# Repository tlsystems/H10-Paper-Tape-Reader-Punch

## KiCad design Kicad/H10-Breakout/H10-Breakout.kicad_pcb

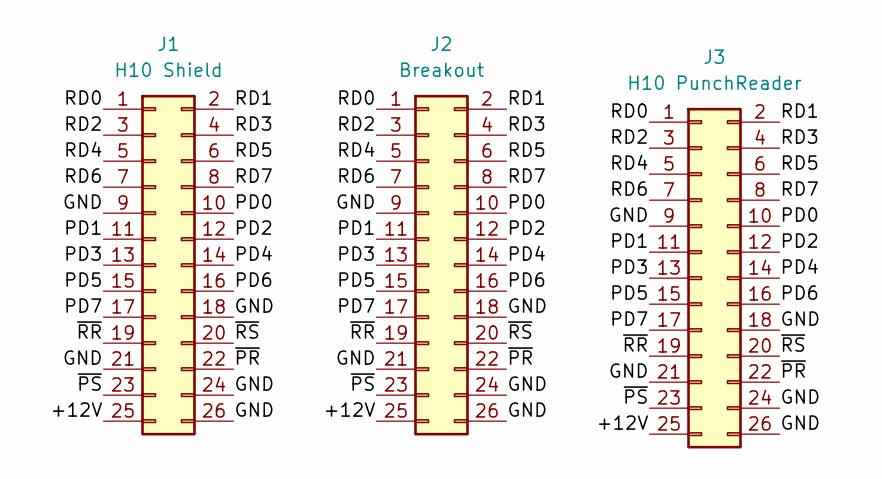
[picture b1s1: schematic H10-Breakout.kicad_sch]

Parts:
J1: H10 Shield; PinSocket_2x13_P2.54mm_Vertical
J2: Breakout; PinHeader_2x13_P2.54mm_Vertical
J3: H10 PunchReader; PinHeader_2x13_P2.54mm_Vertical

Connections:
/+12V: J1.25, J2.25, J3.25
/GND: J1.9, J1.18, J1.21, J1.24, J1.26, J2.9, J2.18, J2.21, J2.24, J2.26, J3.9, J3.18, J3.21, J3.24, J3.26
/PD0: J1.10, J2.10, J3.10
/PD1: J1.11, J2.11, J3.11
/PD2: J1.12, J2.12, J3.12
/PD3: J1.13, J2.13, J3.13
/PD4: J1.14, J2.14, J3.14
/PD5: J1.15, J2.15, J3.15
/PD6: J1.16, J2.16, J3.16
/PD7: J1.17, J2.17, J3.17
/RD0: J1.1, J2.1, J3.1
/RD1: J1.2, J2.2, J3.2
/RD2: J1.3, J2.3, J3.3
/RD3: J1.4, J2.4, J3.4
/RD4: J1.5, J2.5, J3.5
/RD5: J1.6, J2.6, J3.6
/RD6: J1.7, J2.7, J3.7
/RD7: J1.8, J2.8, J3.8
/~PR: J1.22, J2.22, J3.22
/~PS: J1.23, J2.23, J3.23
/~RR: J1.19, J2.19, J3.19
/~RS: J1.20, J2.20, J3.20

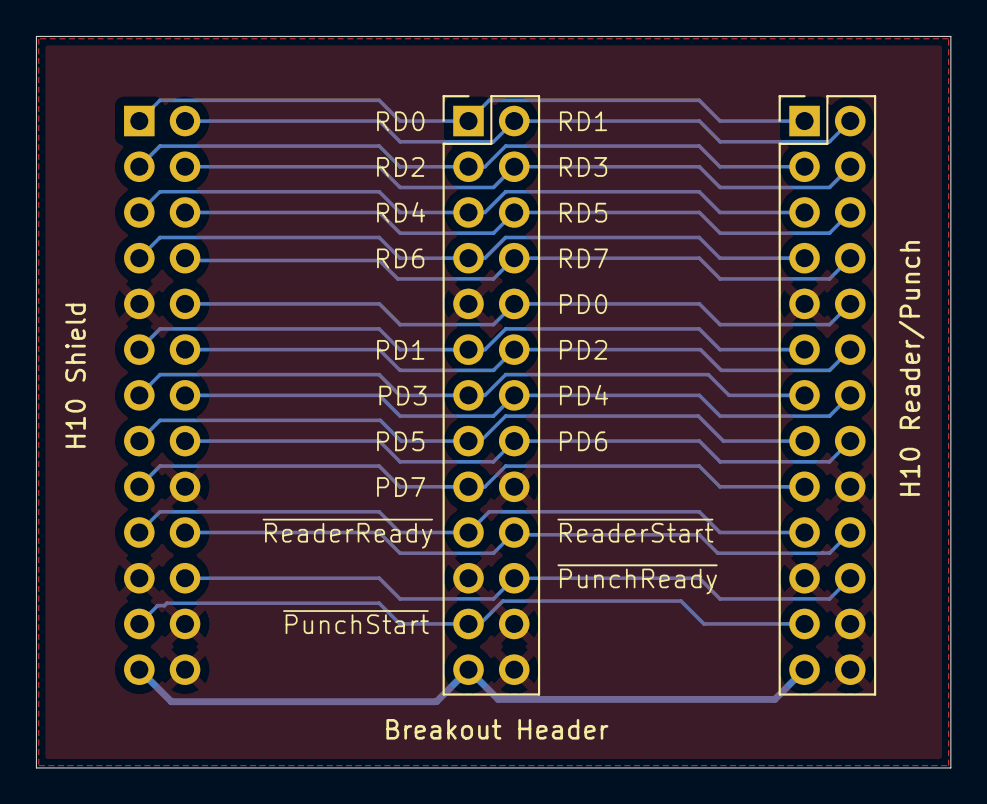
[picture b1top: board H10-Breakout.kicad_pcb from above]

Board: 2 copper layers, 50.8 x 40.6 mm, 3 parts (1 on the bottom side), 22 nets.

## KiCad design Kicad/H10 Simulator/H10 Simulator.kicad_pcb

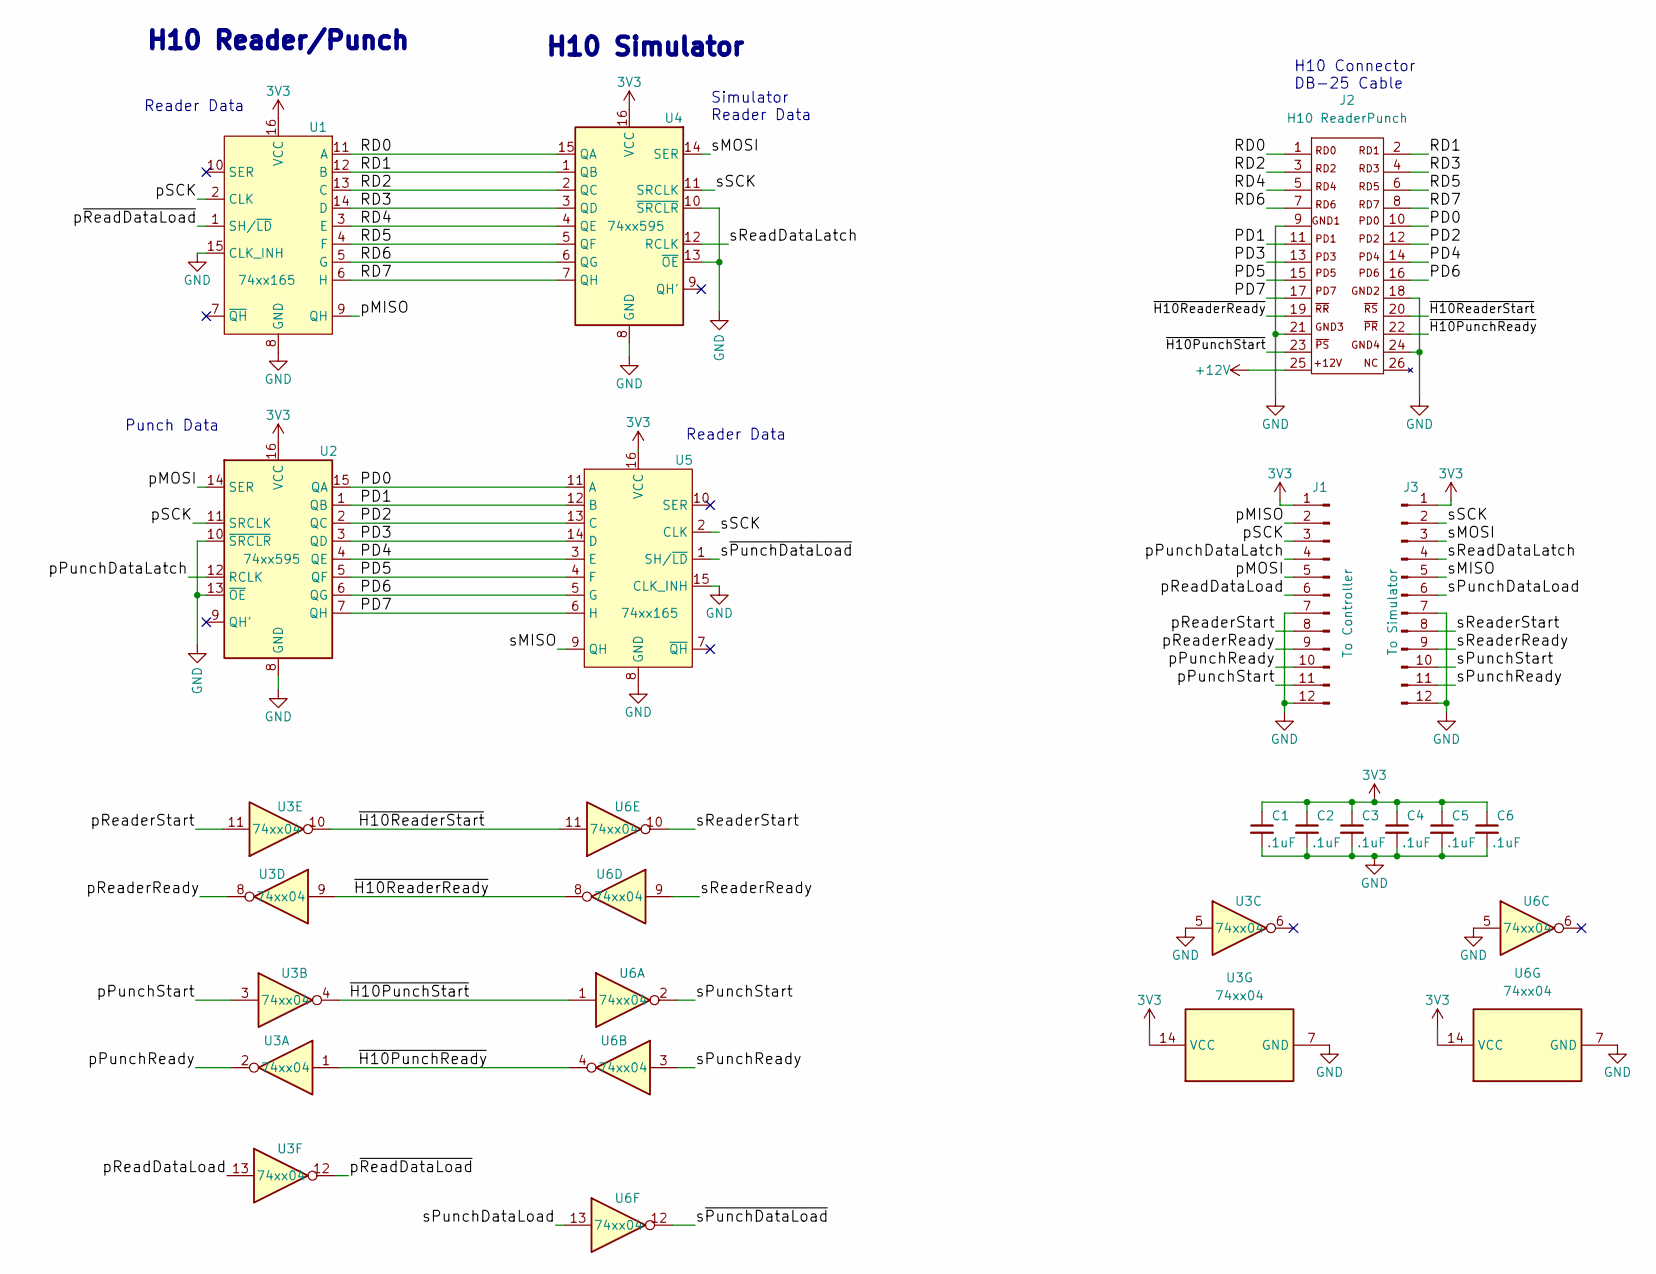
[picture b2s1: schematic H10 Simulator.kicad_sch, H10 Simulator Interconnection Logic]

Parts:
C1, C2, C3, C4, C5, C6: .1uF; C_0603_HandSoldering
J1: To Controller; PinHeader_1x12_P2.54mm_Vertical
J2: H10 ReaderPunch; PinHeader_2x13_P2.54mm_Vertical
J3: To Simulator; PinHeader_1x12_P2.54mm_Vertical
U1, U5: 74xx165; SOIC-16_3.9x9.9mm_P1.27mm
U2, U4: 74xx595; SOIC-16_3.9x9.9mm_P1.27mm
U3, U6: 74xx04; SOIC-14_3.9x8.7mm_P1.27mm

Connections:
3V3: C1.1, C2.1, C3.1, C4.1, C5.1, C6.1, J1.1, J3.1, U1.16 (VCC), U2.16 (VCC), U3.14 (VCC), U4.16 (VCC), U5.16 (VCC), U6.14 (VCC)
+12V: J2.25
/PD0: J2.10, U2.15 (QA), U5.11 (A)
/PD1: J2.11, U2.1 (QB), U5.12 (B)
/PD2: J2.12, U2.2 (QC), U5.13 (C)
/PD3: J2.13, U2.3 (QD), U5.14 (D)
/PD4: J2.14, U2.4 (QE), U5.3 (E)
/PD5: J2.15, U2.5 (QF), U5.4 (F)
/PD6: J2.16, U2.6 (QG), U5.5 (G)
/PD7: J2.17, U2.7 (QH), U5.6 (H)
/RD0: J2.1, U1.11 (A), U4.15 (QA)
/RD1: J2.2 (RD1), U1.12 (B), U4.1 (QB)
/RD2: J2.3, U1.13 (C), U4.2 (QC)
/RD3: J2.4, U1.14 (D), U4.3 (QD)
/RD4: J2.5, U1.3 (E), U4.4 (QE)
/RD5: J2.6, U1.4 (F), U4.5 (QF)
/RD6: J2.7, U1.5 (G), U4.6 (QG)
/RD7: J2.8, U1.6 (H), U4.7 (QH)
/pMISO: J1.2, U1.9 (QH)
/pMOSI: J1.5, U2.14 (SER)
/pPunchDataLatch: J1.4, U2.12 (RCLK)
/pPunchReady: J1.10, U3.2
/pPunchStart: J1.11, U3.3
/pReadDataLoad: J1.6, U3.13
/pReaderReady: J1.9, U3.8
/pReaderStart: J1.8, U3.11
/pSCK: J1.3, U1.2 (CLK), U2.11 (SRCLK)
/p~ReadDataLoad: U1.1 (SH/~LD), U3.12
/sMISO: J3.5, U5.9 (QH)
/sMOSI: J3.3, U4.14 (SER)
/sPunchDataLoad: J3.6, U6.13
/sPunchReady: J3.11, U6.3
/sPunchStart: J3.10, U6.2
/sReadDataLatch: J3.4, U4.12 (RCLK)
/sReaderReady: J3.9, U6.9
/sReaderStart: J3.8, U6.10
/sSCK: J3.2, U4.11 (SRCLK), U5.2 (CLK)
/s~PunchDataLoad: U5.1 (SH/~LD), U6.12
/~H10PunchReady: J2.22, U3.1, U6.4
/~H10PunchStart: J2.23, U3.4, U6.1
/~H10ReaderReady: J2.19, U3.9, U6.8
/~H10ReaderStart: J2.20, U3.10, U6.11
GND: C1.2, C2.2, C3.2, C4.2, C5.2, C6.2, J1.7, J1.12, J2.9, J2.18 (GND2), J2.21, J2.24, J3.7, J3.12, U1.8 (GND), U1.15 (CLK_INH), U2.8 (GND), U2.10 (~SRCLR), U2.13 (~OE), U3.5, U3.7 (GND), U4.8 (GND), U4.10 (~SRCLR), U4.13 (~OE), U5.8 (GND), U5.15 (CLK_INH), U6.5, U6.7 (GND)

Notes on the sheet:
Reader Data
Punch Data
H10 Simulator
Simulator Reader Data
H10 Reader/Punch
H10 Connector DB-25 Cable

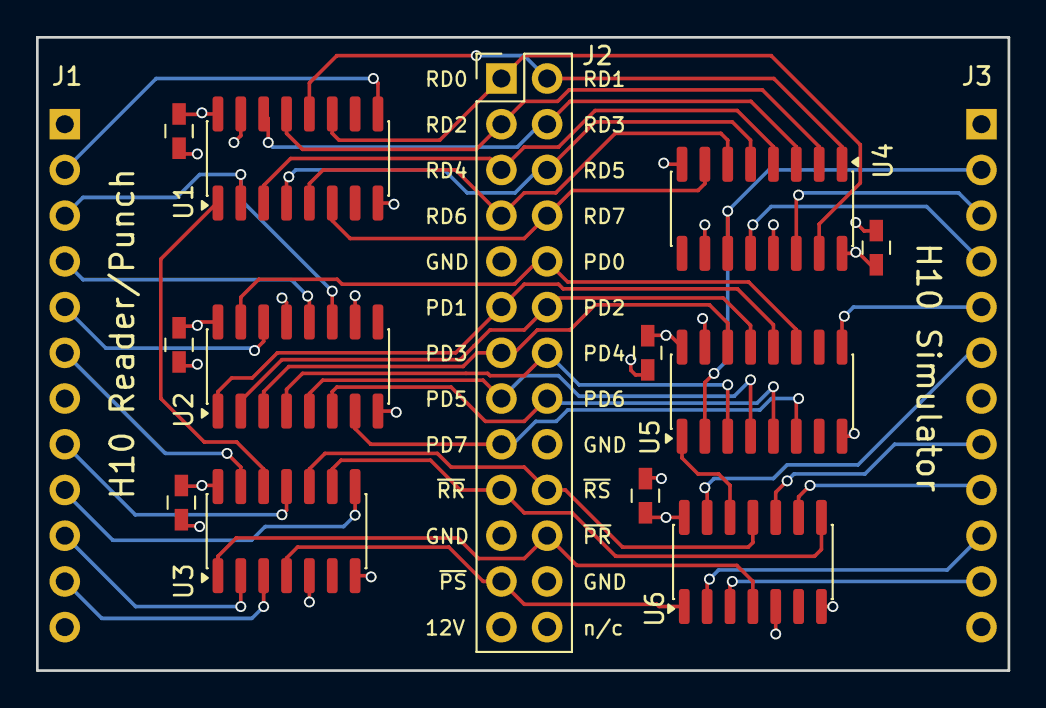
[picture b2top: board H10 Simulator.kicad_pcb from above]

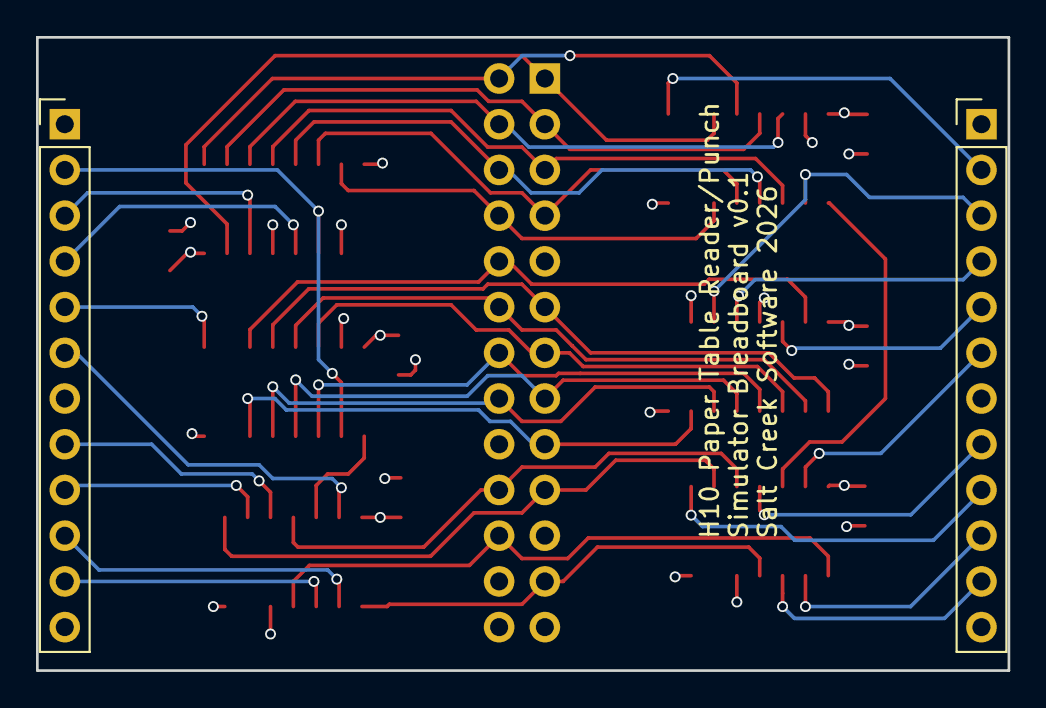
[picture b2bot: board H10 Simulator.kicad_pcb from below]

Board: 4 copper layers, 54.0 x 35.2 mm, 15 parts (2 on the bottom side), 42 nets.

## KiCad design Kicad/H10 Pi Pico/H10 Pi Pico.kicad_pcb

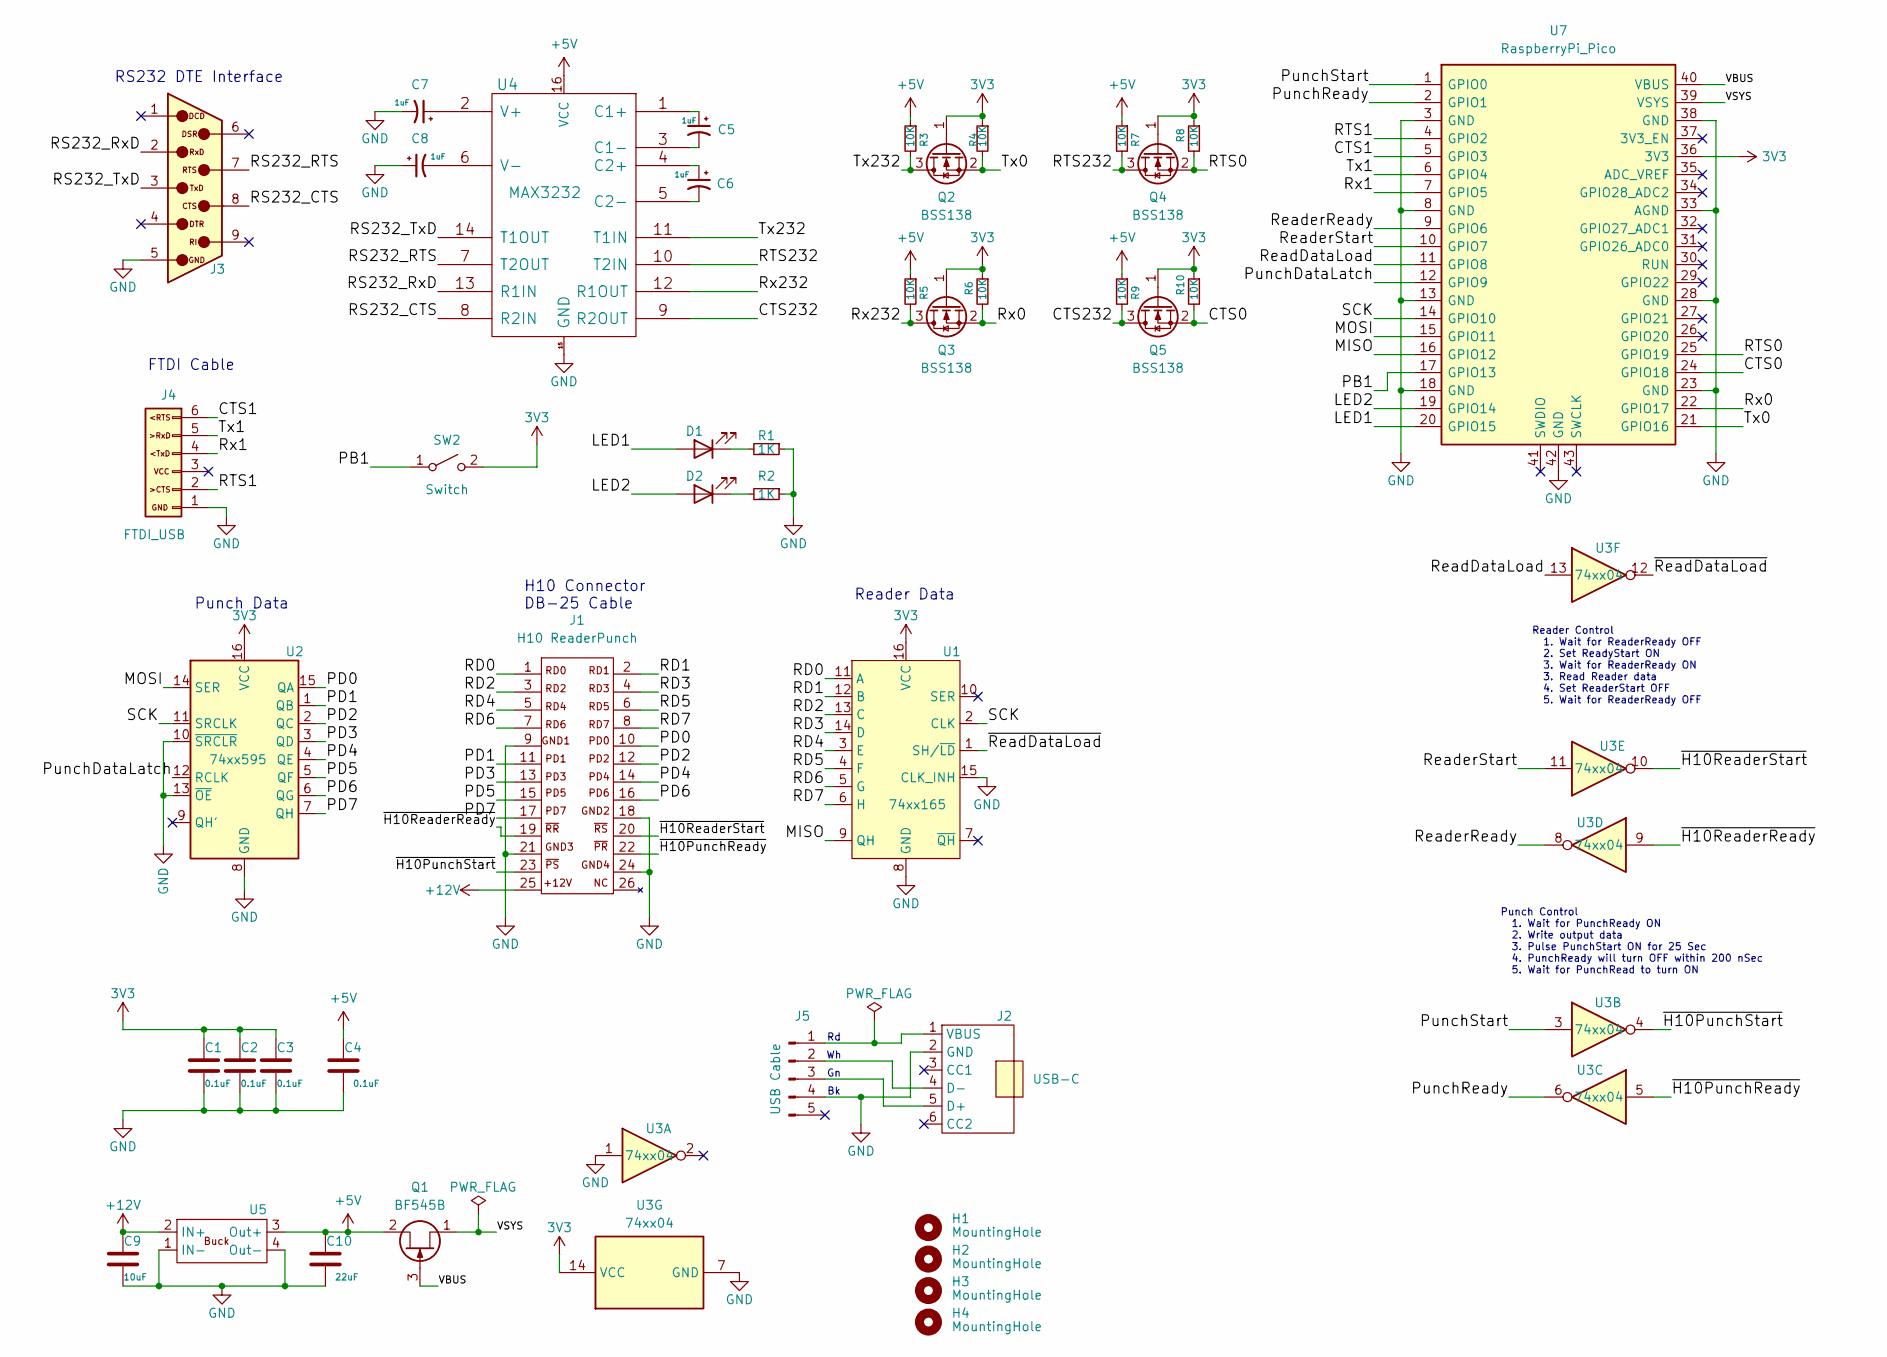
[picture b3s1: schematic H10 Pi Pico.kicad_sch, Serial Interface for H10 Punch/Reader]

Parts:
C1, C2, C3, C4: 0.1uF; C_0603_1608Metric
C5, C6, C7, C8: 1uF; C_0603_1608Metric
C9: 10uF; C_0805_2012Metric
C10: 22uF; C_0805_2012Metric
D1, D2: LED; LED_0805_2012Metric_Pad1.15x1.40mm_HandSolder
H1, H2, H3, H4: MountingHole; MountingHole_3.2mm_M3
J1: H10 ReaderPunch; PinHeader_2x13_P2.54mm_Horizontal
J2: USB-C; USB-C_Breakout
J3: DB-9_RS232_DTE; DSUB-9_Pins_Horizontal_P2.77x2.84mm_EdgePinOffset7.70mm_Hou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
J4: FTDI_USB; PinHeader_1x06_P2.54mm_Vertical
J5: USB Cable; JST_PH_B5B-PH-K_1x05_P2.00mm_Vertical
Q1: BF545B; SOT-23
Q2, Q3, Q4, Q5: BSS138; SOT-23
R1, R2: 1K; R_0603_1608Metric_Pad0.98x0.95mm_HandSolder
R3, R4, R5, R6, R7, R8, R9, R10: 10K; R_0603_1608Metric_Pad0.98x0.95mm_HandSolder
SW2: Switch; SW_PB_Wurth_5x4mm
U1: 74xx165; SOIC-16_3.9x9.9mm_P1.27mm
U2: 74xx595; SOIC-16_3.9x9.9mm_P1.27mm
U3: 74xx04; SOIC-14_3.9x8.7mm_P1.27mm
U4: MAX3232; SOIC-16_3.9x9.9mm_P1.27mm
U5: 5V Buck Converter
U7: RaspberryPi_Pico; RaspberryPi_Pico_Common_THT

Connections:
3V3: C1.1, C2.1, C3.1, Q2.1 (G), Q3.1 (G), Q4.1 (G), Q5.1 (G), R4.1, R6.1, R8.1, R10.1, SW2.2 (B), U1.16 (VCC), U2.16 (VCC), U3.14 (VCC), U7.36 (3V3)
+5V: C4.1, C10.1, Q1.2 (D), R3.1, R5.1, R7.1, R9.1, U4.16 (VCC), U5.3 (Out+)
+12V: C9.1, J1.25, U5.2 (IN+)
/CTS0: Q5.2 (S), R10.2, U7.24 (GPIO18)
/CTS1: J4.6, U7.5 (GPIO3)
/CTS232: Q5.3 (D), R9.2, U4.9 (R2OUT)
/LED1: D1.2 (A), U7.20 (GPIO15)
/LED2: D2.2 (A), U7.19 (GPIO14)
/MISO: U1.9 (QH), U7.16 (GPIO12)
/MOSI: U2.14 (SER), U7.15 (GPIO11)
/PB1: SW2.1 (A), U7.17 (GPIO13)
/PD0: J1.10, U2.15 (QA)
/PD1: J1.11, U2.1 (QB)
/PD2: J1.12, U2.2 (QC)
/PD3: J1.13, U2.3 (QD)
/PD4: J1.14, U2.4 (QE)
/PD5: J1.15, U2.5 (QF)
/PD6: J1.16, U2.6 (QG)
/PD7: J1.17, U2.7 (QH)
/PunchDataLatch: U2.12 (RCLK), U7.12 (GPIO9)
/PunchReady: U3.6, U7.2 (GPIO1)
/PunchStart: U3.3, U7.1 (GPIO0)
/RD0: J1.1, U1.11 (A)
/RD1: J1.2 (RD1), U1.12 (B)
/RD2: J1.3, U1.13 (C)
/RD3: J1.4, U1.14 (D)
/RD4: J1.5, U1.3 (E)
/RD5: J1.6, U1.4 (F)
/RD6: J1.7, U1.5 (G)
/RD7: J1.8, U1.6 (H)
/RS232_CTS: J3.8, U4.8 (R2IN)
/RS232_RTS: J3.7, U4.7 (T2OUT)
/RS232_RxD: J3.2, U4.13 (R1IN)
/RS232_TxD: J3.3, U4.14 (T1OUT)
/RTS0: Q4.2 (S), R8.2, U7.25 (GPIO19)
/RTS1: J4.2, U7.4 (GPIO2)
/RTS232: Q4.3 (D), R7.2, U4.10 (T2IN)
/ReadDataLoad: U3.13, U7.11 (GPIO8)
/ReaderReady: U3.8, U7.9 (GPIO6)
/ReaderStart: U3.11, U7.10 (GPIO7)
/Rx0: Q3.2 (S), R6.2, U7.22 (GPIO17)
/Rx1: J4.4, U7.7 (GPIO5)
/Rx232: Q3.3 (D), R5.2, U4.12 (R1OUT)
/SCK: U1.2 (CLK), U2.11 (SRCLK), U7.14 (GPIO10)
/Tx0: Q2.2 (S), R4.2, U7.21 (GPIO16)
/Tx1: J4.5, U7.6 (GPIO4)
/Tx232: Q2.3 (D), R3.2, U4.11 (T1IN)
/VBUS: Q1.3 (G), U7.40 (VBUS)
/VSYS: Q1.1 (S), U7.39 (VSYS)
/~H10PunchReady: J1.22, U3.5
/~H10PunchStart: J1.23, U3.4
/~H10ReaderReady: J1.19, U3.9
/~H10ReaderStart: J1.20, U3.10
/~ReadDataLoad: U1.1 (SH/~LD), U3.12
GND: C1.2, C2.2, C3.2, C4.2, C7.2, C8.1, C9.2, C10.2, J1.9, J1.18 (GND2), J1.21, J1.24, J2.2 (GND), J3.5, J4.1, J5.4, R1.1, R2.1, U1.8 (GND), U1.15 (CLK_INH), U2.8 (GND), U2.10 (~SRCLR), U2.13 (~OE), U3.1, U3.7 (GND), U4.15 (GND), U5.1 (IN-), U5.4 (Out-), U7.3 (GND), U7.8 (GND), U7.13 (GND), U7.18 (GND), U7.23 (GND), U7.28 (GND), U7.33 (AGND), U7.38 (GND), U7.42 (GND)
unnamed: D1.1 (K), R1.2
unnamed: D2.1 (K), R2.2
unnamed: J2.5 (D+), J5.3
unnamed: J2.4 (D-), J5.2
unnamed: J2.1 (VBUS), J5.1
unnamed: C5.1, U4.1 (C1+)
unnamed: C5.2, U4.3 (C1-)
unnamed: C6.1, U4.4 (C2+)
unnamed: C6.2, U4.5 (C2-)
unnamed: C7.1, U4.2 (V+)
unnamed: C8.2, U4.6 (V-)

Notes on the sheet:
Reader Data
Punch Control 1. Wait for PunchReady ON 2. Write output data 3. Pulse PunchStart ON for 25 Sec 4. PunchReady will turn OFF within 200 nSec 5. Wait for PunchRead to turn ON
RS232 DTE Interface
Punch Data
Reader Control 1. Wait for ReaderReady OFF 2. Set ReadyStart ON 3. Wait for ReaderReady ON 3. Read Reader data 4. Set ReaderStart OFF 5. Wait for ReaderReady OFF
FTDI Cable
H10 Connector DB-25 Cable

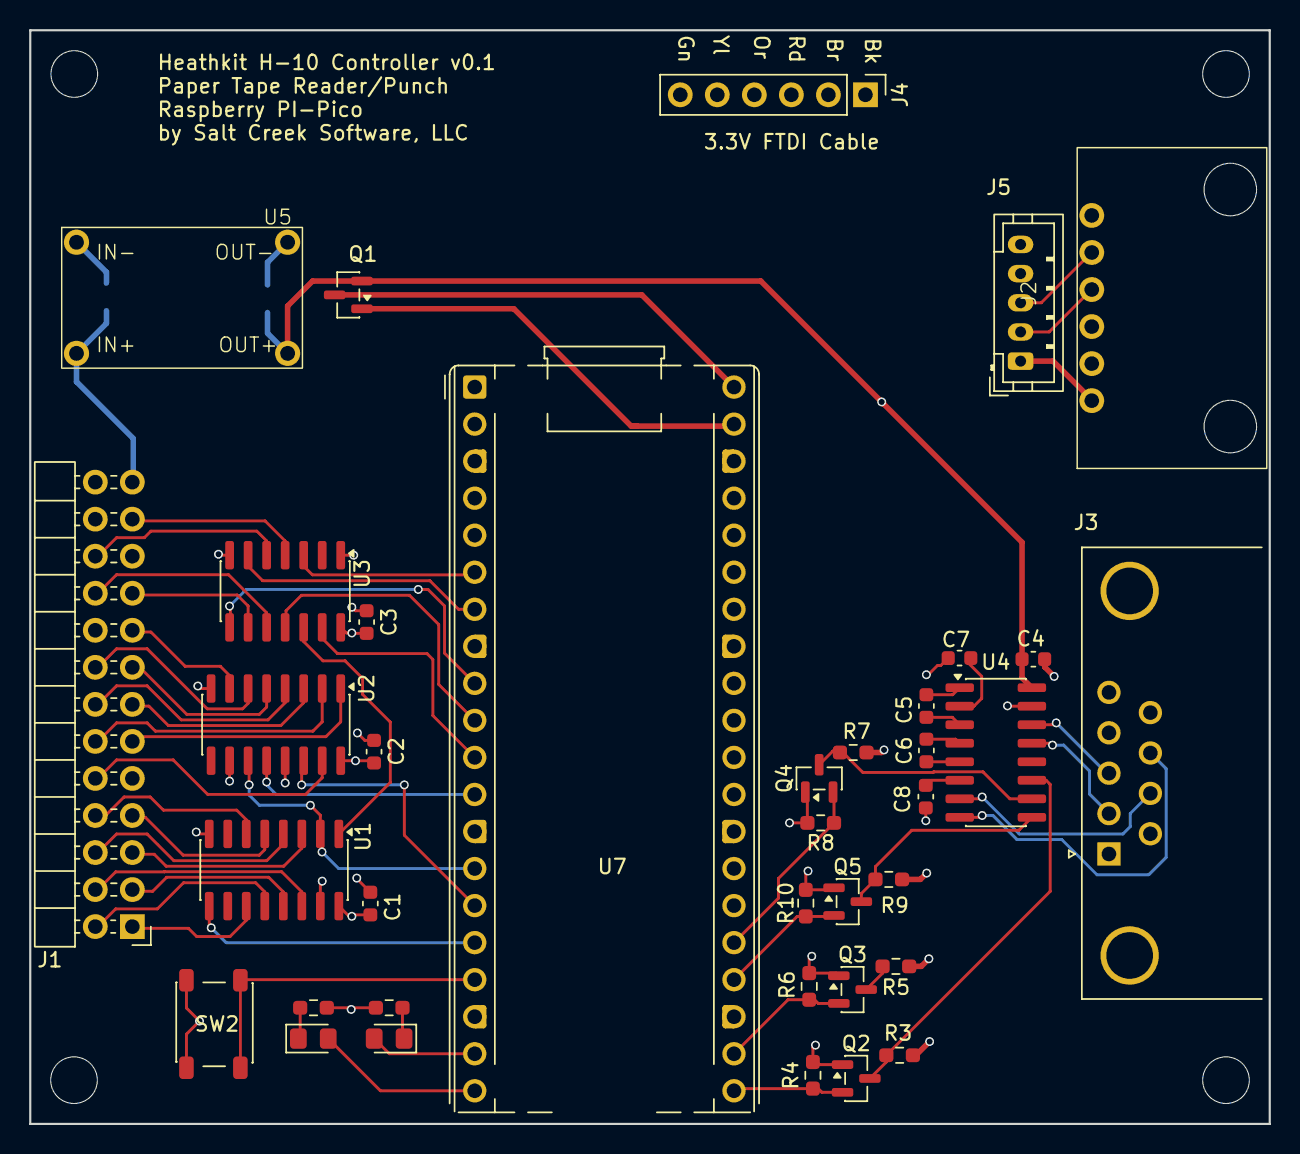
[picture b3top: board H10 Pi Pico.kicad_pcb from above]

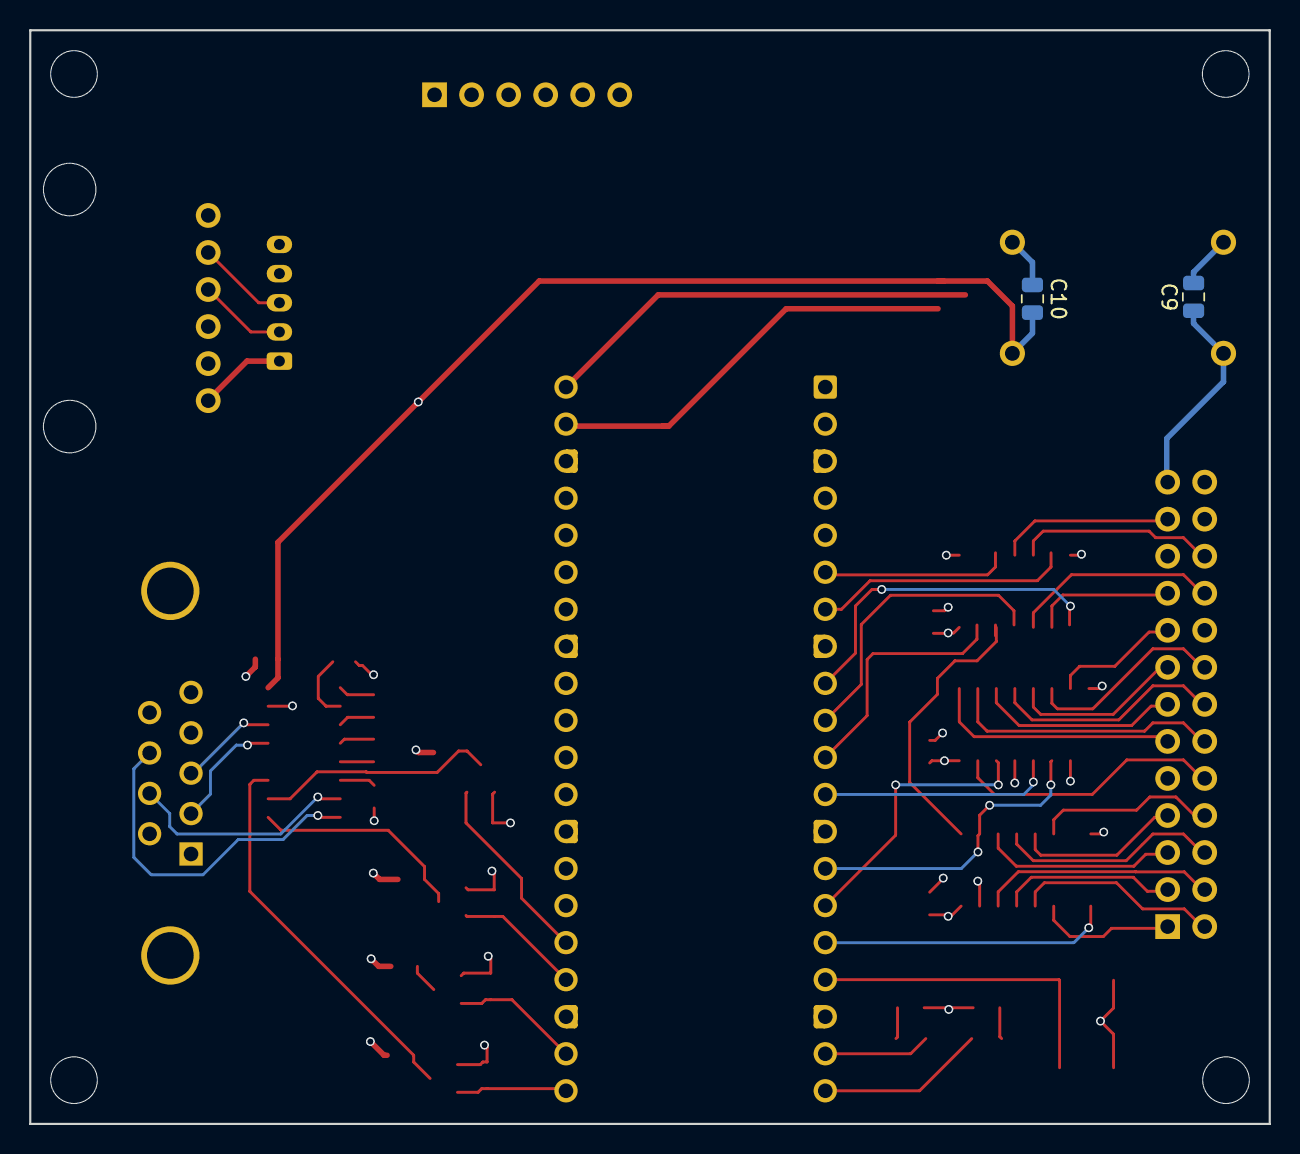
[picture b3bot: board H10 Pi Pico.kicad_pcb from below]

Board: 4 copper layers, 85.0 x 75.0 mm, 43 parts (2 on the bottom side), 66 nets.

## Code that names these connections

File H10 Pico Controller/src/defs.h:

// H10 Controls
#define PunchStart      4   // Starts H10 Punch cycle
#define PunchReady      5   // H10 punch is ready to cycle
#define ReaderReady     6   // H10 read data is available
#define ReaderStart     7   // Start H10 Read cycle

// SPI Bus
#define ReadDataLoad    8    // Load H10 Reader data
#define PunchDataLatch  9    // Latch H10 Punch data
#define SCK             10   // SPI Clock
#define MOSI            11   // SPI MasterOutSlaveIn
#define MISO            12   // SPI MasterInSlaveOut

// Debug
#define PB1     13
#define LED1    14
#define LED2    15

// RS-232 Port
#define RS232_TX  16
#define RS232_RX  17
#define RS232_CTS 18
#define RS232_RTS 19

// internal pico pins
#define POWER_SAVE   23 // Output to enable power save mode
#define VBUS_SENSE   24 // Input to monitor presense of VBUS
#define PICO_LED     25 // Output to control onboard LED
#define VSYS_MONITOR 29 // Analog Input to monotor VSYS

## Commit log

2026-03-19 Initial Pico Controller commit
2026-03-19 Initial commit of H10 Controller and H10 Simulator board Kicad projects
2026-03-19 Rename gerber zip file
2026-03-19 Add gerbers directory to ignore list
2026-03-20 Flip J1 and J3 to back of board, add labels to J2, bump to v0.2
2026-03-22 Cleanup library names
2026-03-22 Move library files into the project src and include directories
2026-03-24 Add H1-_Font, H10_Manager, iCom, Com Add H10 documentation Modified H10_Controller to use CircularBuffer
2026-03-24 Add Kicad H10-Breakout project
2026-03-25 Add Teensy 4.1 version of H10 project to repository
2026-03-29 Basic command processing working. H10 Controller does not yet try to talk with hardware.
